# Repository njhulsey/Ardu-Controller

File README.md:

# Ardu-Controller
Arduino inspired hand-held controller!

Contains all of the basic circuitry for an arduino Uno as well as some addition devices:
  - Adafruit OLED
  - Joystick
  - 4 Dip Buttons
  - Buzzer
  - lipo battery charger
  - LEDs
  - Serial (which is used to communicate with a PC)
  
As for the code there are two projects included in this repository. 
The first project is used for controlling a mouse with the game controller using python's serial class.
The second project is snake which can be played on the controller itself.

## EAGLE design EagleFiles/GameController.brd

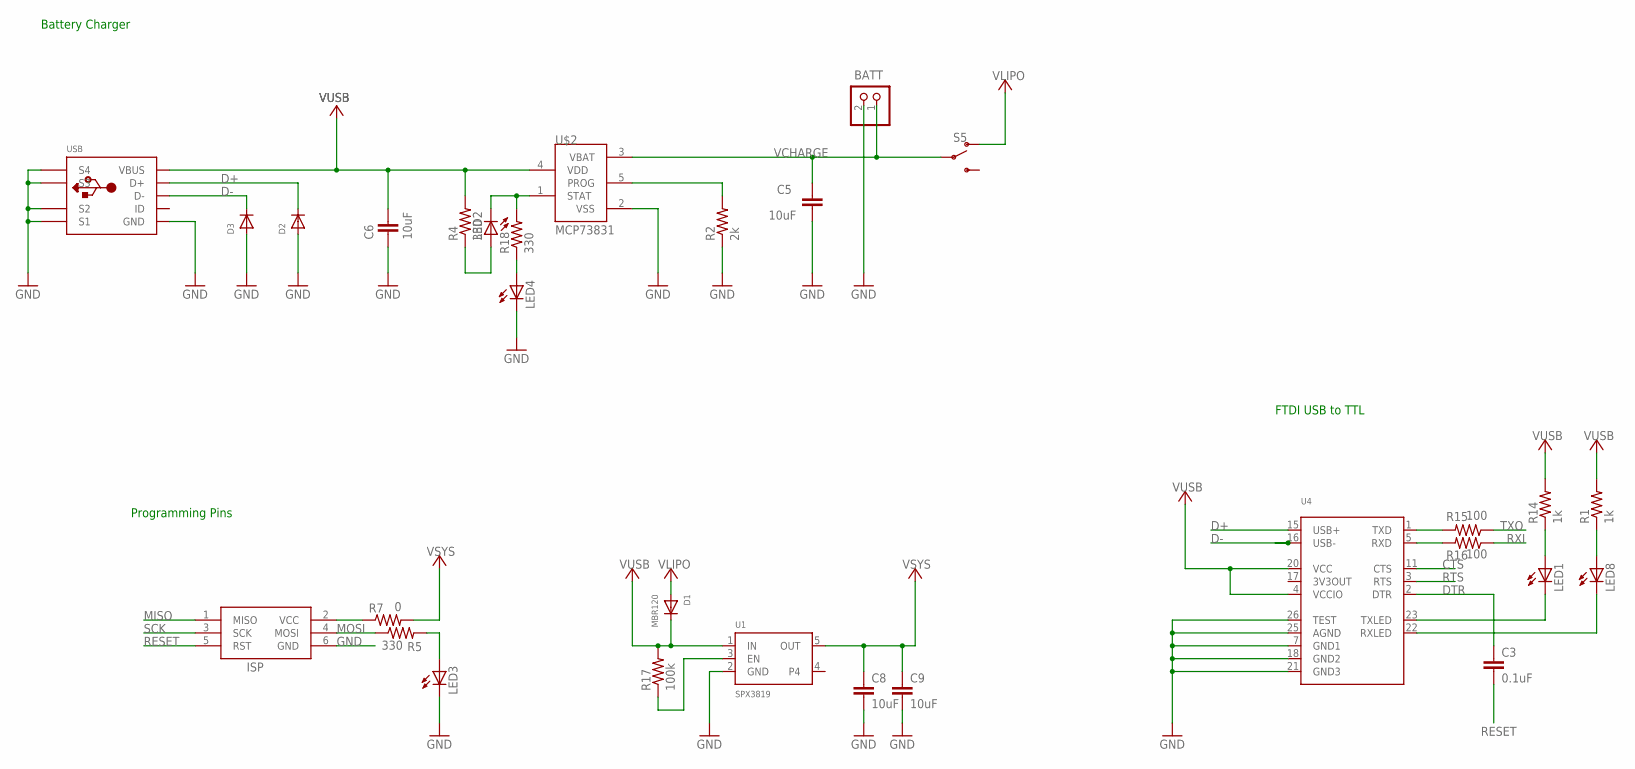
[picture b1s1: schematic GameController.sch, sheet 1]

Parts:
BATT: JST_2PIN-SMT-RA; JST-PH-2-SMT-RA
C3: 0.1uF; C0805
C5, C6, C8, C9: 10uF; C0805
D1: MBR120; SOD-123
D2, D3: DIODESOD-323; SOD-323
ISP: AVRISP-6; AVRISP
LED1, LED2, LED3, LED4, LED8: LEDCHIPLED_0805; CHIPLED_0805
R1, R14: 1k; R0805
R2: 2k; R0805
R4, R5, R18: 330; R0805
R7: 0; R0805
R15, R16: 100; R0805
R17: 100k; R0805
S5: SWITCH-SPDT-SMD-RIGHT-ANGLE; SWITCH_SPST_SMD_A
U1: SPX3819; SOT23-5
U4: FT232RLSSOP28; SSOP28DB
U$2: MCP73831; SOT23-5L
USB: USBMINIB; USB-MINIB

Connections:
3V3OUT: U4.17 (3V3OUT)
CTS: U4.11 (CTS)
D+: D2.C, U4.15 (USB+), USB.D+
D-: D3.C, U4.16 (USB-), USB.D-
DTR: C3.1, U4.2 (DTR)
GND: BATT.2 (1), C5.2, C6.2, C8.2, C9.2, D2.A, D3.A, ISP.6 (GND), LED3.C, LED4.C, R2.1, U1.2 (GND), U4.7 (GND1), U4.18 (GND2), U4.21 (GND3), U4.25 (AGND), U4.26 (TEST), U$2.2 (VSS), USB.GND, USB.GND1 (S1), USB.GND2 (S2), USB.GND3 (S3), USB.GND4 (S4); also elsewhere on the board
MISO: ISP.1 (MISO); also elsewhere on the board
MOSI: ISP.4 (MOSI), R5.1; also elsewhere on the board
unnamed: LED3.A, R5.2
unnamed: LED2.A, R4.1
unnamed: R15.2, U4.1 (TXD)
unnamed: LED2.C, R18.2, U$2.1 (STAT)
unnamed: R2.2, U$2.5 (PROG)
unnamed: R16.2, U4.5 (RXD)
unnamed: ISP.2 (VCC), R7.1
unnamed: LED4.A, R18.1
unnamed: R17.1, U1.3 (EN)
unnamed: LED1.C, U4.23 (TXLED)
unnamed: LED8.C, U4.22 (RXLED)
unnamed: LED1.A, R14.1
unnamed: LED8.A, R1.1
RESET: C3.2, ISP.5 (RST); also elsewhere on the board
RTS: U4.3 (RTS)
RXI: R16.1; also elsewhere on the board
SCK: ISP.3 (SCK); also elsewhere on the board
TXO: R15.1; also elsewhere on the board
VCHARGE: BATT.1 (2), C5.1, S5.2, U$2.3 (VBAT)
VLIPO: D1.A, S5.1 (O)
VSYS: C8.1, C9.1, R7.2, U1.5 (OUT); also elsewhere on the board
VUSB: C6.1, D1.C, R1.2, R4.2, R14.2, R17.2, U1.1 (IN), U4.4 (VCCIO), U4.20 (VCC), U$2.4 (VDD), USB.VBUS

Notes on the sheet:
Battery Charger
FTDI USB to TTL
Programming Pins

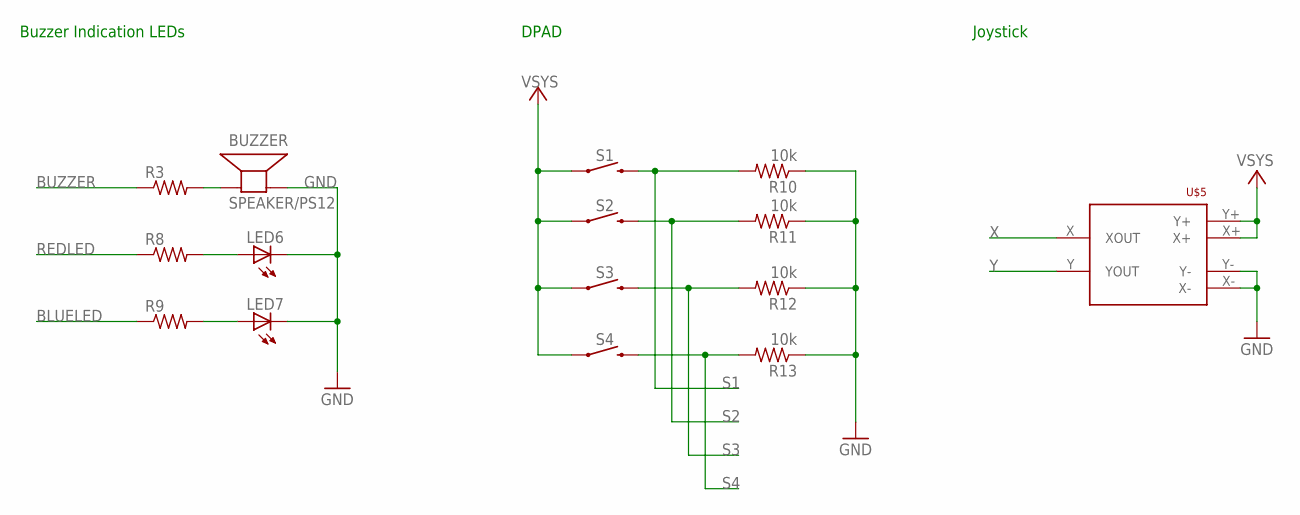
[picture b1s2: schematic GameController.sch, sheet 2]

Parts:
BUZZER: SPEAKER/PS12; PS12
LED6, LED7: LEDCHIPLED_0805; CHIPLED_0805
R3, R8, R9: R-US_R0805; R0805
R10, R11, R12, R13: 10k; R0805
S1, S2, S3, S4: MOMENTARY-SWITCH-SPST-PTH-6.0MM-KIT; TACTILE_SWITCH_PTH_6.0MM_KIT
U$5: JOYSTICK_ANALOG

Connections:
BLUELED: R9.1; also elsewhere on the board
BUZZER: R3.1; also elsewhere on the board
GND: BUZZER.P$2 (-), LED6.C, LED7.C, R10.1, R11.1, R12.1, R13.1, U$5.X-, U$5.Y-; also elsewhere on the board
unnamed: BUZZER.P$1 (+), R3.2
unnamed: LED6.A, R8.2
unnamed: LED7.A, R9.2
REDLED: R8.1; also elsewhere on the board
S1: R10.2, S1.3 (2); also elsewhere on the board
S2: R11.2, S2.3 (2); also elsewhere on the board
S3: R12.2, S3.3 (2); also elsewhere on the board
S4: R13.2, S4.3 (2); also elsewhere on the board
VSYS: S1.1, S2.1, S3.1, S4.1, U$5.X+, U$5.Y+; also elsewhere on the board
X: U$5.X (XOUT); also elsewhere on the board
Y: U$5.Y (YOUT); also elsewhere on the board

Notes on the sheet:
Buzzer Indication LEDs
DPAD
Joystick

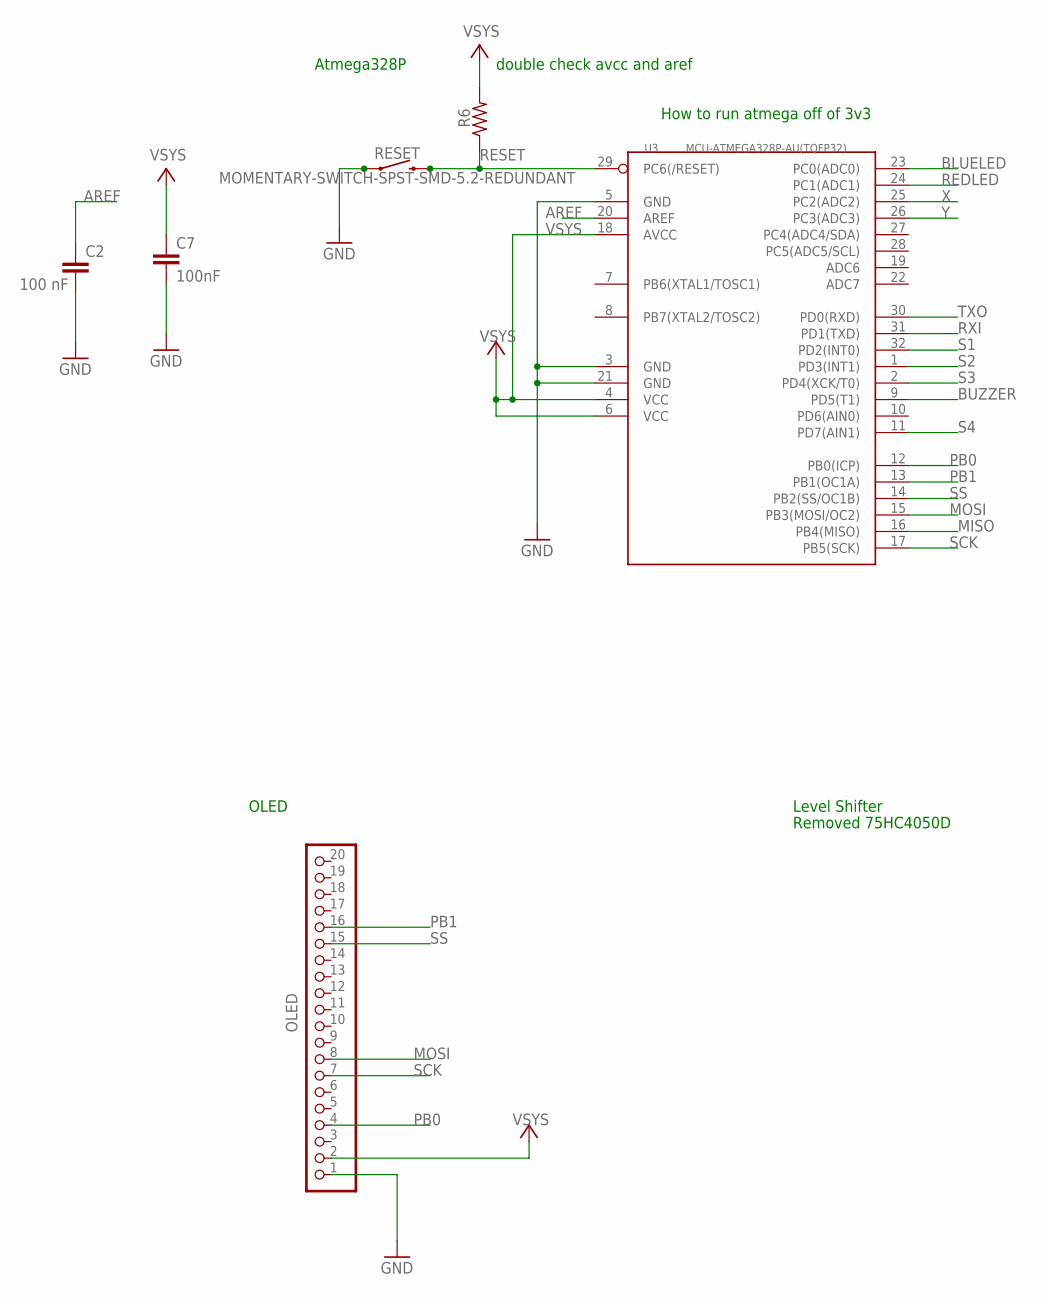
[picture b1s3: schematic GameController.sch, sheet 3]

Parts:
C2: 100 nF; C0805
C7: 100nF; C0805
OLED: PINHD-1X20-BIG; 1X20-BIG
R6: R-US_R0805; R0805
RESET: MOMENTARY-SWITCH-SPST-SMD-5.2-REDUNDANT; TACTILE_SWITCH_SMD_5.2MM
U3: MCU-ATMEGA328P-AU(TQFP32); TQFP32-0.8-7X7MM

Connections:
AREF: C2.1, U3.20 (AREF)
BLUELED: U3.23 (PC0(ADC0)); also elsewhere on the board
BUZZER: U3.9 (PD5(T1)); also elsewhere on the board
GND: C2.2, C7.2, OLED.1, RESET.1, RESET.2 (1), U3.3 (GND), U3.5 (GND), U3.21 (GND); also elsewhere on the board
MISO: U3.16 (PB4(MISO)); also elsewhere on the board
MOSI: OLED.8, U3.15 (PB3(MOSI/OC2)); also elsewhere on the board
PB0: OLED.4, U3.12 (PB0(ICP))
PB1: OLED.16, U3.13 (PB1(OC1A))
REDLED: U3.24 (PC1(ADC1)); also elsewhere on the board
RESET: R6.1, RESET.3 (2), RESET.4 (2), U3.29 (PC6(/RESET)); also elsewhere on the board
RXI: U3.31 (PD1(TXD)); also elsewhere on the board
S1: U3.32 (PD2(INT0)); also elsewhere on the board
S2: U3.1 (PD3(INT1)); also elsewhere on the board
S3: U3.2 (PD4(XCK/T0)); also elsewhere on the board
S4: U3.11 (PD7(AIN1)); also elsewhere on the board
SCK: OLED.7, U3.17 (PB5(SCK)); also elsewhere on the board
SS: OLED.15, U3.14 (PB2(SS/OC1B))
TXO: U3.30 (PD0(RXD)); also elsewhere on the board
VSYS: C7.1, OLED.2, R6.2, U3.4 (VCC), U3.6 (VCC), U3.18 (AVCC); also elsewhere on the board
X: U3.25 (PC2(ADC2)); also elsewhere on the board
Y: U3.26 (PC3(ADC3)); also elsewhere on the board

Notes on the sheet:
double check avcc and aref
Atmega328P
OLED
Level Shifter
How to run atmega off of 3v3
Removed 75HC4050D

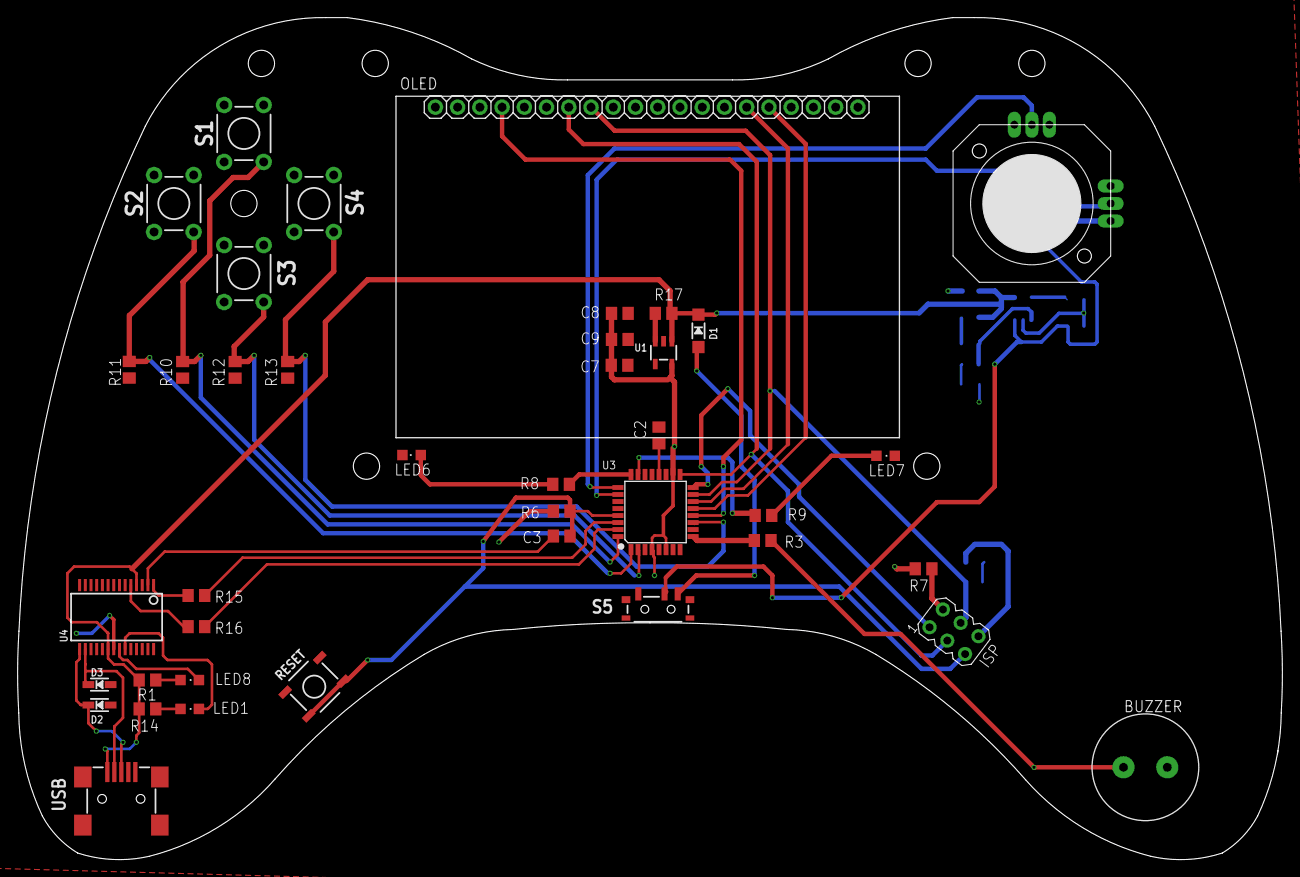
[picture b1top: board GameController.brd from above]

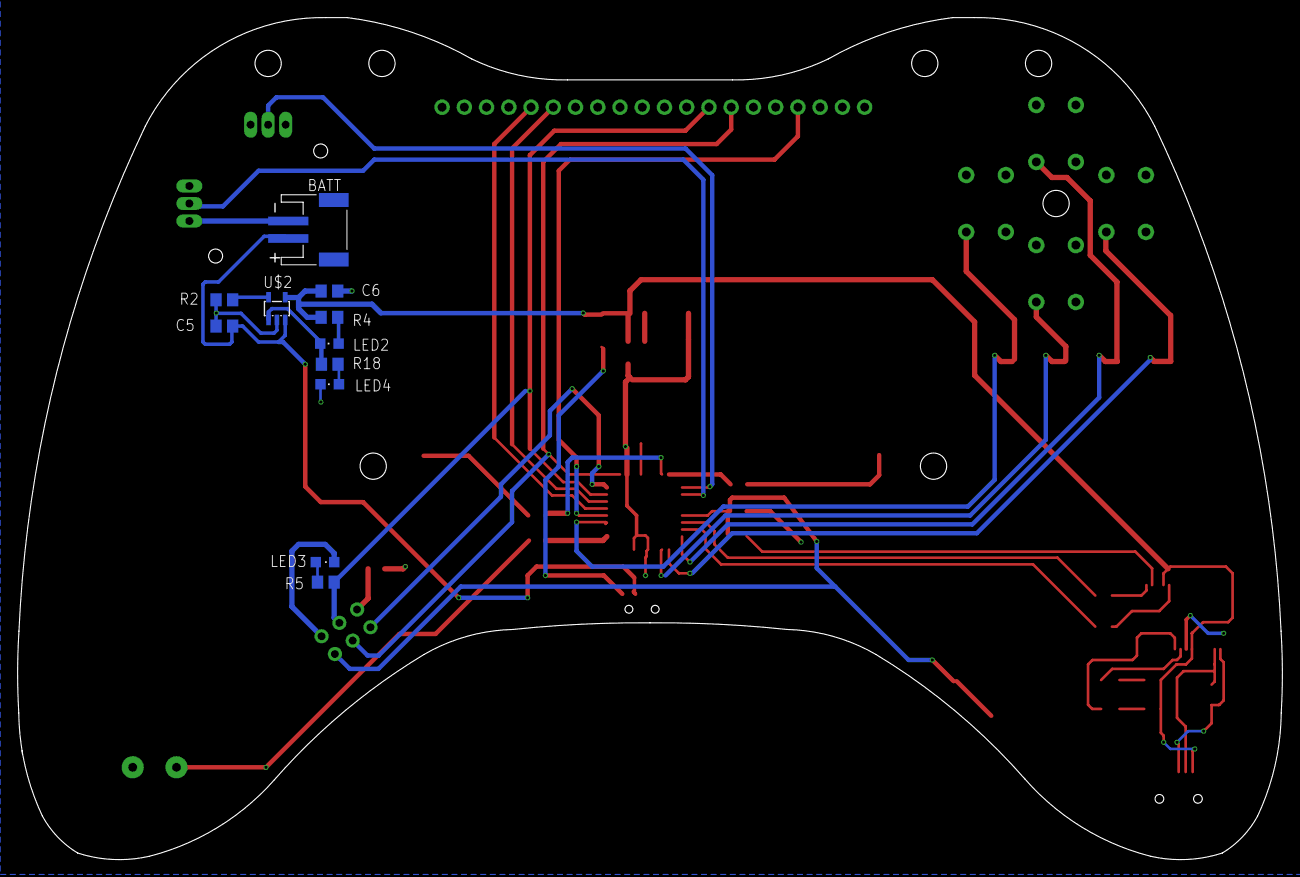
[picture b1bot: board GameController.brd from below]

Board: 2 copper layers, 144.5 x 96.2 mm, 51 parts (11 on the bottom side), 43 nets.

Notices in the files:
parts and their libraries:
SparkFun-Switches: Licensing: Creative Commons ShareAlike 4.0 International - https://creativecommons.org/licenses/by-sa/4.0
microbuilder: This work is placed in the public domain, and may be freely used for commercial and non-commercial work with the following conditions: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
